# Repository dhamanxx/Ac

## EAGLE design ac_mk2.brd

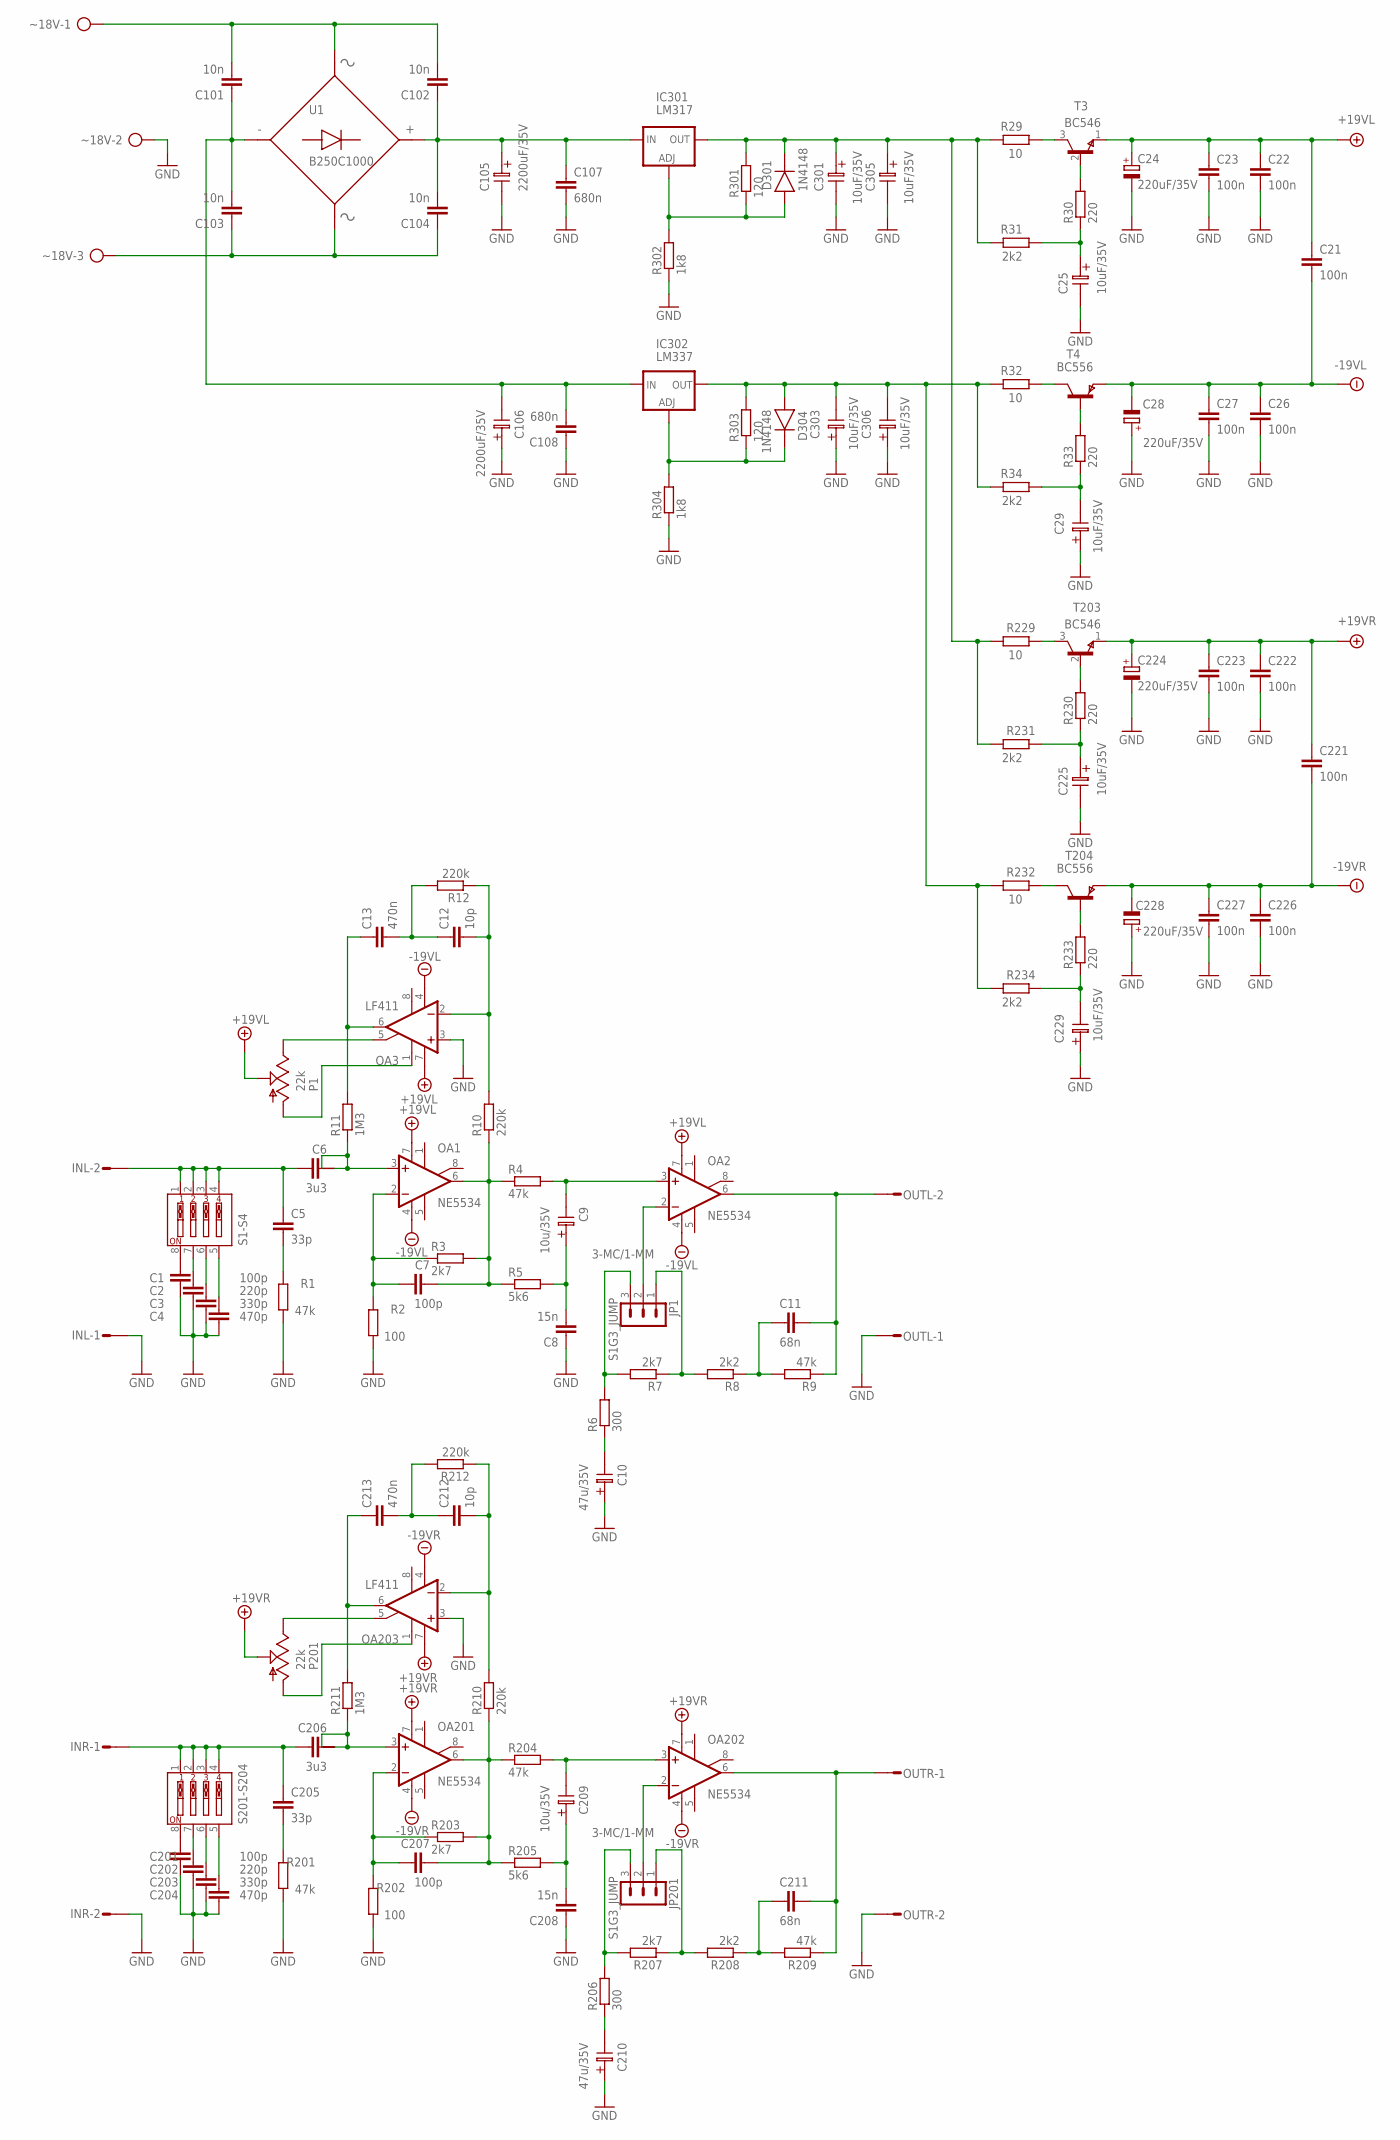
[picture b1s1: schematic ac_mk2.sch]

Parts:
C1, C7, C201, C207: 100p; C5B3.5
C2, C202: 220p; C5B3.5
C3, C203: 330p; C5B3.5
C4, C204: 470p; C5B3.5
C5, C205: 33p; KERAMICKY_RM5
C6, C206: 3u3; C10-15B6
C8, C208: 15n; C5B3.5
C9, C209: 10u/35V; CT07
C10, C210: 47u/35V; CT07
C11, C211: 68n; C5B3.5
C12, C212: 10p; KERAMICKY_RM5
C13, C213: 470n; C5B5.5
C21, C22, C23, C26, C27, C221, C222, C223, C226, C227: 100n; C5B3.5
C24, C28, C224, C228: 220uF/35V; ELEKTROLITICKY_RM3,5-8
C25, C29, C225, C229, C301, C303, C305, C306: 10uF/35V; CT07
C101, C102, C103, C104: 10n; C5B3.5
C105, C106: 2200uF/35V; E160
C107, C108: 680n; C5B5.5
D301, D304: 1N4148; DO41
IC301: LM317; 317TS
IC302: LM337; 337TS
INL: S02P
INR: S02P
JP1, JP201: S1G3_JUMP; S1G3_JUM
OA1, OA2, OA201, OA202: NE5534; DIL08
OA3, OA203: LF411; DIL08
OUTL: S02P
OUTR: S02P
P1, P201: 22k; S64W
R1, R4, R9, R201, R204, R209: 47k; 0207/10
R2, R202: 100; 0207/10
R3, R7, R203, R207: 2k7; 0207/10
R5, R205: 5k6; 0207/10
R6, R206: 300; 0207/10
R8, R31, R34, R208, R231, R234: 2k2; 0207/10
R10, R12, R210, R212: 220k; 0207/10
R11, R211: 1M3; 0207/10
R29, R32, R229, R232: 10; 0207/10
R30, R33, R230, R233: 220; 0207/10
R301, R303: 120; 0207/10
R302, R304: 1k8; 0207/10
S1-S4, S201-S204: DIP4X; EDG-04
T3, T203: BC546; TO-92C
T4, T204: BC556; TO-92C
U1: B250C1000; DB1
~18V: AK500/3

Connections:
+19VL: C21.1, C22.1, C23.1, C24.P$2 (+), OA1.7 (V+), OA2.7 (V+), OA3.7 (V+), P1.S, T3.1 (E)
+19VR: C221.1, C222.1, C223.1, C224.P$2 (+), OA201.7 (V+), OA202.7 (V+), OA203.7 (V+), P201.S, T203.1 (E)
-19VL: C21.2, C26.1, C27.1, C28.P$1 (-), OA1.4 (V-), OA2.4 (V-), OA3.4 (V-), T4.1 (E)
-19VR: C221.2, C226.1, C227.1, C228.P$1 (-), OA201.4 (V-), OA202.4 (V-), OA203.4 (V-), T204.1 (E)
GND: C1.2, C2.2, C3.2, C4.2, C8.1, C10.1, C22.2, C23.2, C24.P$1 (-), C25.2, C26.2, C27.2, C28.P$2 (+), C29.1, C105.2, C106.1, C107.2, C108.1, C201.2, C202.2, C203.2, C204.2, C208.1, C210.1, C222.2, C223.2, C224.P$1 (-), C225.2, C226.2, C227.2, C228.P$2 (+), C229.1, C301.2, C303.1, C305.2, C306.1, INL.1, INR.2, OA3.3 (+IN), OA203.3 (+IN), OUTL.1, OUTR.2, R1.1, R2.1, R201.1, R202.1, R302.1, R304.1, ~18V.2
unnamed: JP1.2, OA2.2 (-IN)
unnamed: C10.2, R6.1
unnamed: C101.1, C103.2, C106.2, C108.2, IC302.2 (IN), U1.2
unnamed: C102.1, C104.2, C105.1, C107.1, IC301.3 (IN), U1.1
unnamed: C5.P$2 (2), R1.2
unnamed: C6.2, C6.3, OA1.3 (+IN), R11.1
unnamed: C7.1, OA1.2 (-IN), R2.2, R3.1
unnamed: C7.2, OA1.6 (OUT), R3.2, R4.1, R5.1, R10.1
unnamed: C8.2, C9.1, R5.2
unnamed: C11.1, OA2.6 (OUT), OUTL.2, R9.1
unnamed: JP1.3, R6.2, R7.2
unnamed: C5.P$1 (1), C6.1, INL.2, S1-S4.1, S1-S4.2, S1-S4.3, S1-S4.4
unnamed: C1.1, S1-S4.8
unnamed: C12.P$2 (2), OA3.2 (-IN), R10.2, R12.1
unnamed: JP1.1, R7.1, R8.2
unnamed: C11.2, R8.1, R9.2
unnamed: C13.1, OA3.6 (OUT), R11.2
unnamed: C12.P$1 (1), C13.2, R12.2
unnamed: OA3.5 (ON2), P1.E
unnamed: OA3.1 (ON1), P1.A
unnamed: C205.P$1 (1), C206.1, INR.1, S201-S204.1, S201-S204.2, S201-S204.3, S201-S204.4
unnamed: C201.1, S201-S204.8
unnamed: C2.1, S1-S4.7
unnamed: C3.1, S1-S4.6
unnamed: C4.1, S1-S4.5
unnamed: C202.1, S201-S204.7
unnamed: C203.1, S201-S204.6
unnamed: C204.1, S201-S204.5
unnamed: C205.P$2 (2), R201.2
unnamed: D301.A, IC301.1 (ADJ), R301.1, R302.2
unnamed: C206.2, C206.3, OA201.3 (+IN), R211.1
unnamed: C207.1, OA201.2 (-IN), R202.2, R203.1
unnamed: C207.2, OA201.6 (OUT), R203.2, R204.1, R205.1, R210.1
unnamed: C208.2, C209.1, R205.2
unnamed: C211.1, OA202.6 (OUT), OUTR.1, R209.1
unnamed: JP201.2, OA202.2 (-IN)
unnamed: C210.2, R206.1
unnamed: JP201.3, R206.2, R207.2
unnamed: JP201.1, R207.1, R208.2
unnamed: C211.2, R208.1, R209.2
unnamed: C212.P$2 (2), OA203.2 (-IN), R210.2, R212.1
unnamed: C213.1, OA203.6 (OUT), R211.2
unnamed: C212.P$1 (1), C213.2, R212.2
unnamed: OA203.5 (ON2), P201.E
unnamed: OA203.1 (ON1), P201.A
unnamed: D304.K, IC302.1 (ADJ), R303.1, R304.2
unnamed: C301.1, C305.1, D301.K, IC301.2 (OUT), R29.2, R31.2, R229.2, R231.2, R301.2
unnamed: C303.2, C306.2, D304.A, IC302.3 (OUT), R32.2, R34.2, R232.2, R234.2, R303.2
unnamed: R30.2, T3.2 (B)
unnamed: R29.1, T3.3 (C)
unnamed: C25.1, R30.1, R31.1
unnamed: R33.2, T4.2 (B)
unnamed: R32.1, T4.3 (C)
unnamed: C29.2, R33.1, R34.1
unnamed: R230.2, T203.2 (B)
unnamed: R229.1, T203.3 (C)
unnamed: C225.1, R230.1, R231.1
unnamed: R233.2, T204.2 (B)
unnamed: R232.1, T204.3 (C)
unnamed: C229.2, R233.1, R234.1
unnamed: C101.2, C102.2, U1.3, ~18V.1
unnamed: C103.1, C104.1, U1.4, ~18V.3
OA1: C209.2, OA202.3 (+IN), R204.2
OA2: C9.2, OA2.3 (+IN), R4.2

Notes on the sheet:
3-MC/1-MM

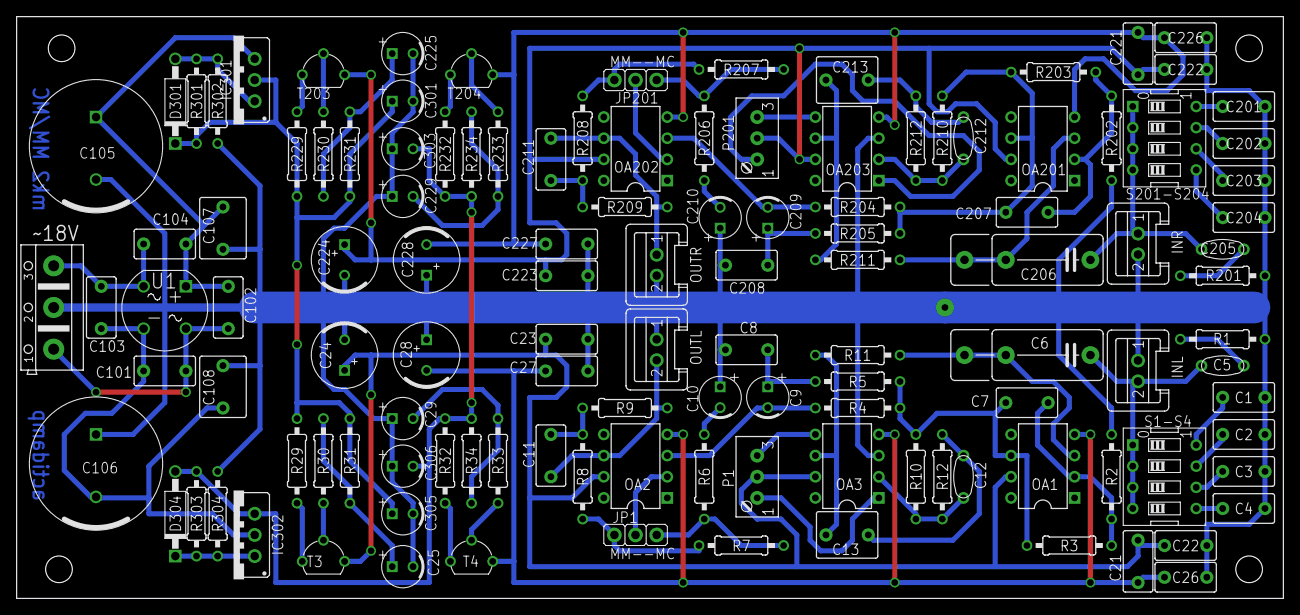
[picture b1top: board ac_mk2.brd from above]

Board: 2 copper layers, 152.1 x 69.8 mm, 122 parts (0 on the bottom side), 69 nets.
